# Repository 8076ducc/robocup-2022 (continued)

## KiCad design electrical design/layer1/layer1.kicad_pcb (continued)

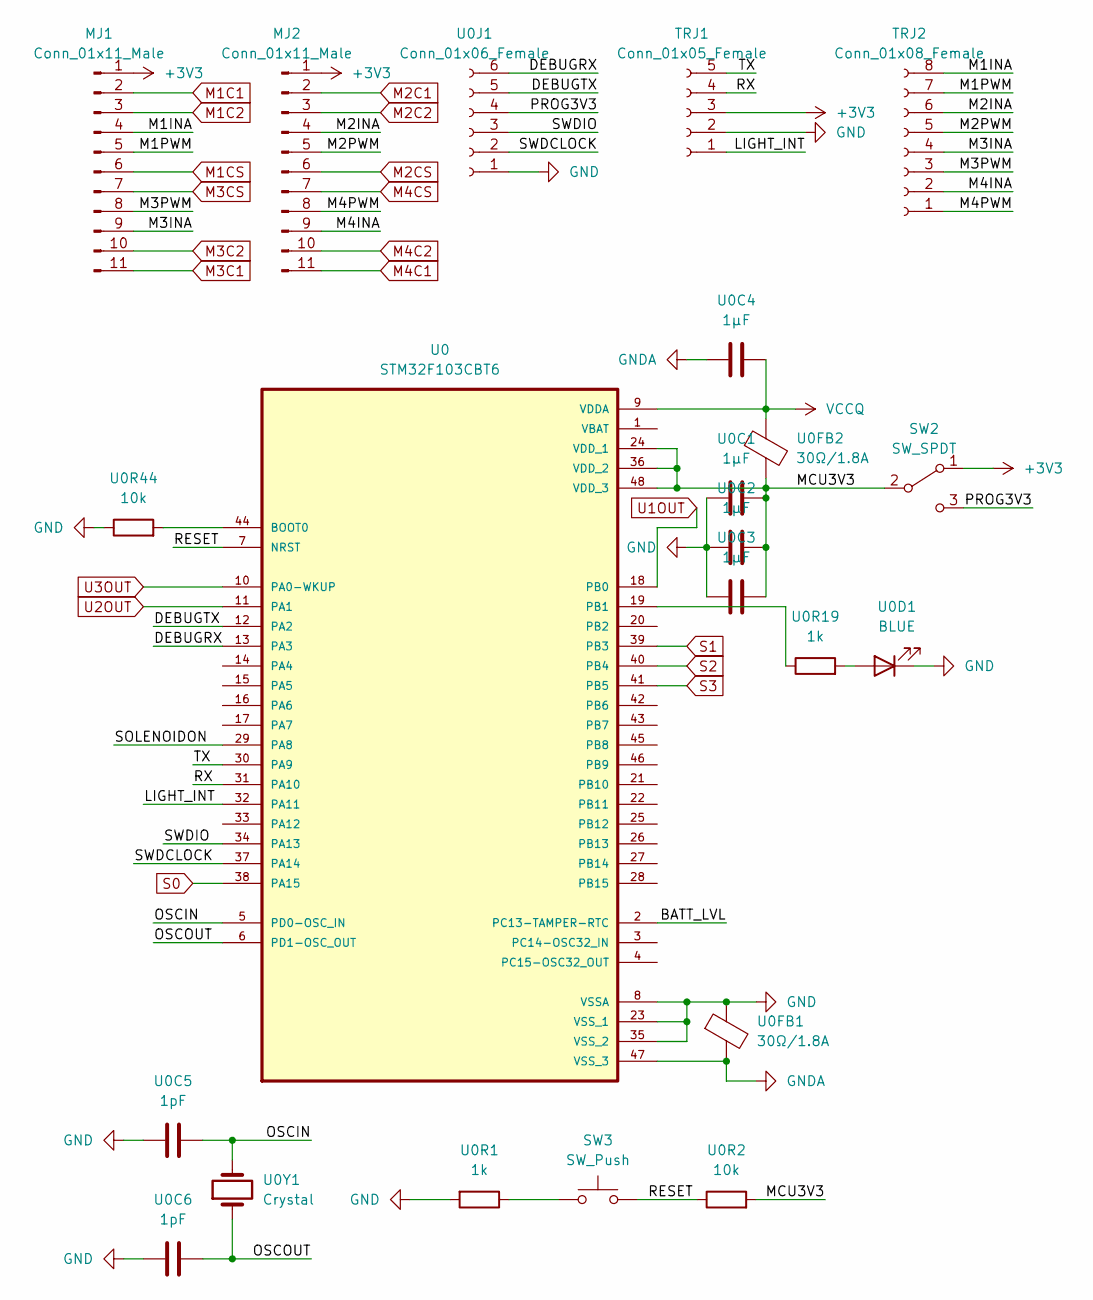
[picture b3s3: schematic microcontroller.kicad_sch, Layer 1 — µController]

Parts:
MJ1, MJ2: Conn_01x11_Male; 1X11_LOCK
SW2: SW_SPDT; SWITCH_SPDT_PTH_11.6X4.0MM_LOCK
SW3: SW_Push; SW_Push_SPST_NO_Alps_SKRK
TRJ1: Conn_01x05_Female; JST_SH_BM05B-SRSS-TB_1x05-1MP_P1.00mm_Vertical
TRJ2: Conn_01x08_Female; JST_SH_BM08B-SRSS-TB_1x08-1MP_P1.00mm_Vertical
U0: STM32F103CBT6; QFP50P900X900X160-48N; PARTREV 10
U0C1, U0C2, U0C3, U0C4: 1µF; 0603
U0C5, U0C6: 1pF; 0603
U0D1: BLUE; LED-0603
U0FB1, U0FB2: 30Ω/1.8A; 0603
U0J1: Conn_01x06_Female; JST_SH_BM06B-SRSS-TB_1x06-1MP_P1.00mm_Vertical
U0R1, U0R19: 1k; 0603
U0R2, U0R44: 10k; 0603
U0Y1: Crystal; CRYSTAL-SMD-5X3.2-2PAD

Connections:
+3V3: MJ1.1, MJ2.1, SW2.1 (A), TRJ1.3; also elsewhere on the board
/microcontroller/BATT_LVL: U0.2 (PC13-TAMPER-RTC)
/microcontroller/DEBUGRX: U0.13 (PA3), U0J1.6
/microcontroller/DEBUGTX: U0.12 (PA2), U0J1.5
/microcontroller/LIGHT_INT: TRJ1.1, U0.32 (PA11)
/microcontroller/M1INA: MJ1.4, TRJ2.8
/microcontroller/M1PWM: MJ1.5, TRJ2.7
/microcontroller/M2INA: MJ2.4, TRJ2.6
/microcontroller/M2PWM: MJ2.5, TRJ2.5
/microcontroller/M3INA: MJ1.9, TRJ2.4
/microcontroller/M3PWM: MJ1.8, TRJ2.3
/microcontroller/M4INA: MJ2.9, TRJ2.2
/microcontroller/M4PWM: MJ2.8, TRJ2.1
/microcontroller/MCU3V3: SW2.2 (B), U0.24 (VDD_1), U0.36 (VDD_2), U0.48 (VDD_3), U0C1.2, U0C2.2, U0C3.2, U0FB2.2, U0R2.2
/microcontroller/OSCIN: U0.5 (PD0-OSC_IN), U0C5.2, U0Y1.2
/microcontroller/OSCOUT: U0.6 (PD1-OSC_OUT), U0C6.2, U0Y1.1
/microcontroller/PROG3V3: SW2.3 (C), U0J1.4
/microcontroller/RESET: SW3.2, U0.7 (NRST), U0R2.1
/microcontroller/RX: TRJ1.4, U0.31 (PA10)
/microcontroller/SOLENOIDON: U0.29 (PA8)
/microcontroller/SWDCLOCK: U0.37 (PA14), U0J1.2
/microcontroller/SWDIO: U0.34 (PA13), U0J1.3
/microcontroller/TX: TRJ1.5, U0.30 (PA9)
GND: TRJ1.2, U0.8 (VSSA), U0.23 (VSS_1), U0.35 (VSS_2), U0C1.1, U0C2.1, U0C3.1, U0C5.1, U0C6.1, U0D1.1 (K), U0FB1.1, U0J1.1, U0R1.2, U0R44.1; also elsewhere on the board
GNDA: U0.47 (VSS_3), U0C4.1, U0FB1.2
M1C1: MJ1.2; also elsewhere on the board
M1C2: MJ1.3; also elsewhere on the board
M1CS: MJ1.6; also elsewhere on the board
M2C1: MJ2.2; also elsewhere on the board
M2C2: MJ2.3; also elsewhere on the board
M2CS: MJ2.6; also elsewhere on the board
M3C1: MJ1.11; also elsewhere on the board
M3C2: MJ1.10; also elsewhere on the board
M3CS: MJ1.7; also elsewhere on the board
M4C1: MJ2.11; also elsewhere on the board
M4C2: MJ2.10; also elsewhere on the board
M4CS: MJ2.7; also elsewhere on the board
unnamed: SW3.1, U0R1.1
unnamed: U0.19 (PB1), U0R19.1
unnamed: U0.44 (BOOT0), U0R44.2
unnamed: U0D1.2 (A), U0R19.2
S0: U0.38 (PA15); also elsewhere on the board
S1: U0.39 (PB3); also elsewhere on the board
S2: U0.40 (PB4); also elsewhere on the board
S3: U0.41 (PB5); also elsewhere on the board
U1OUT: U0.18 (PB0); also elsewhere on the board
U2OUT: U0.11 (PA1); also elsewhere on the board
U3OUT: U0.10 (PA0-WKUP); also elsewhere on the board
VCCQ: U0.9 (VDDA), U0C4.2, U0FB2.1; also elsewhere on the board

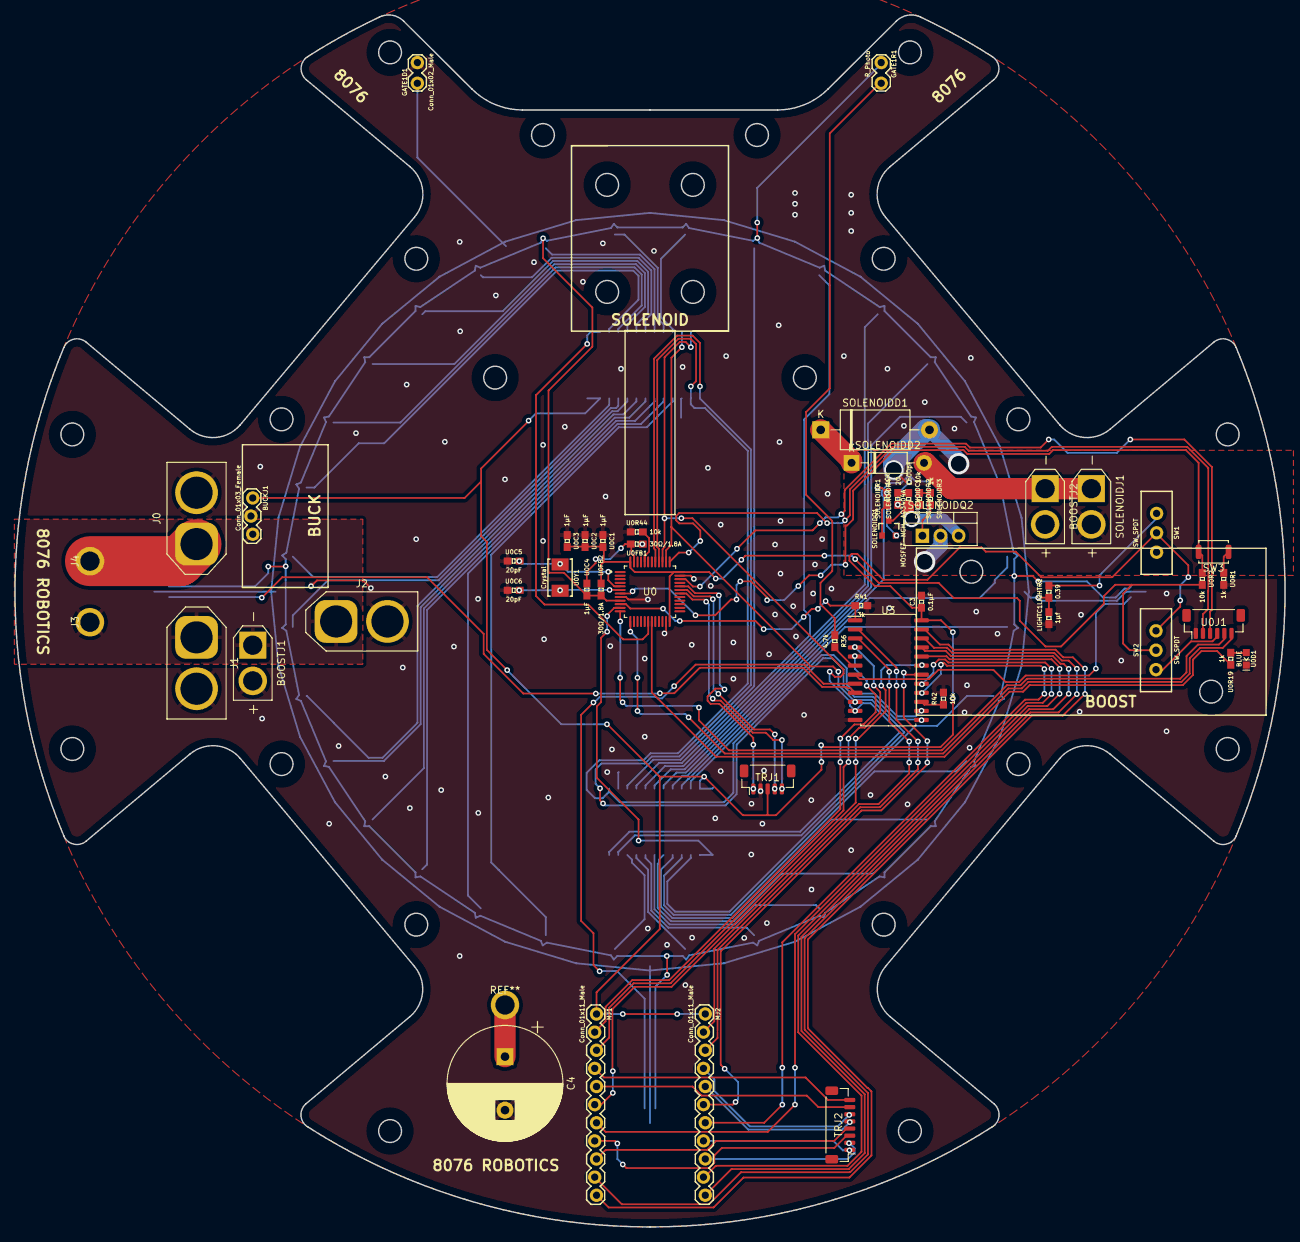
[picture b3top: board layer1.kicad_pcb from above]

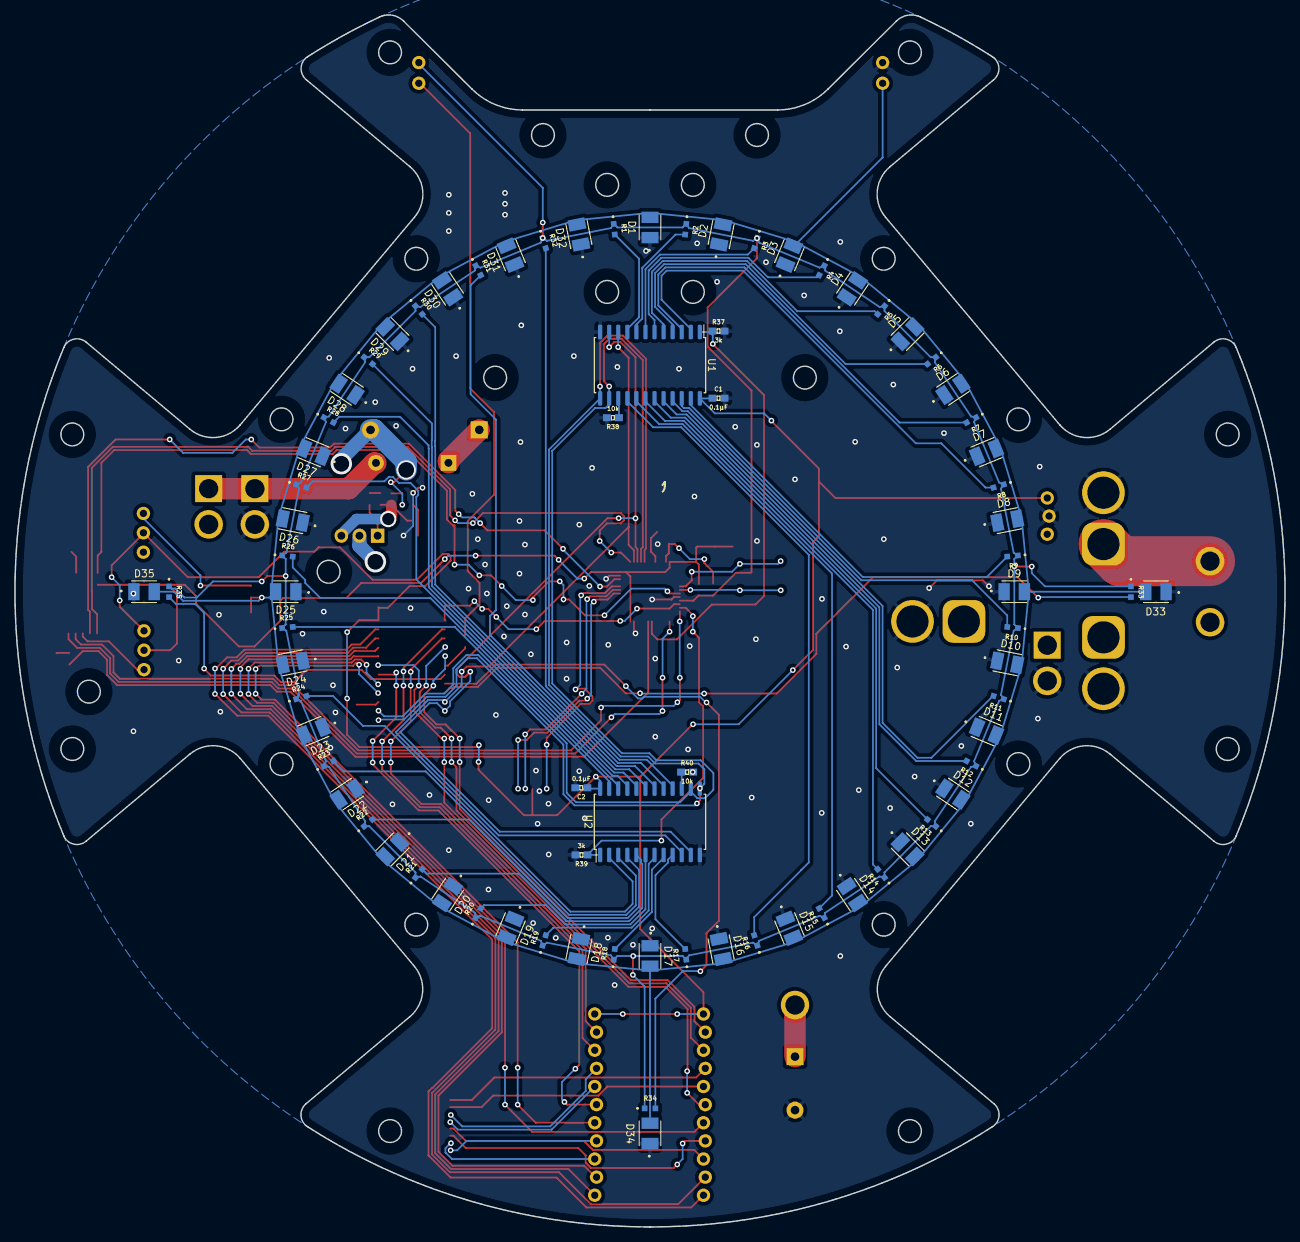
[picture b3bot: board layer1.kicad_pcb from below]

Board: 2 copper layers, 178.0 x 169.8 mm, 129 parts (78 on the bottom side), 99 nets.

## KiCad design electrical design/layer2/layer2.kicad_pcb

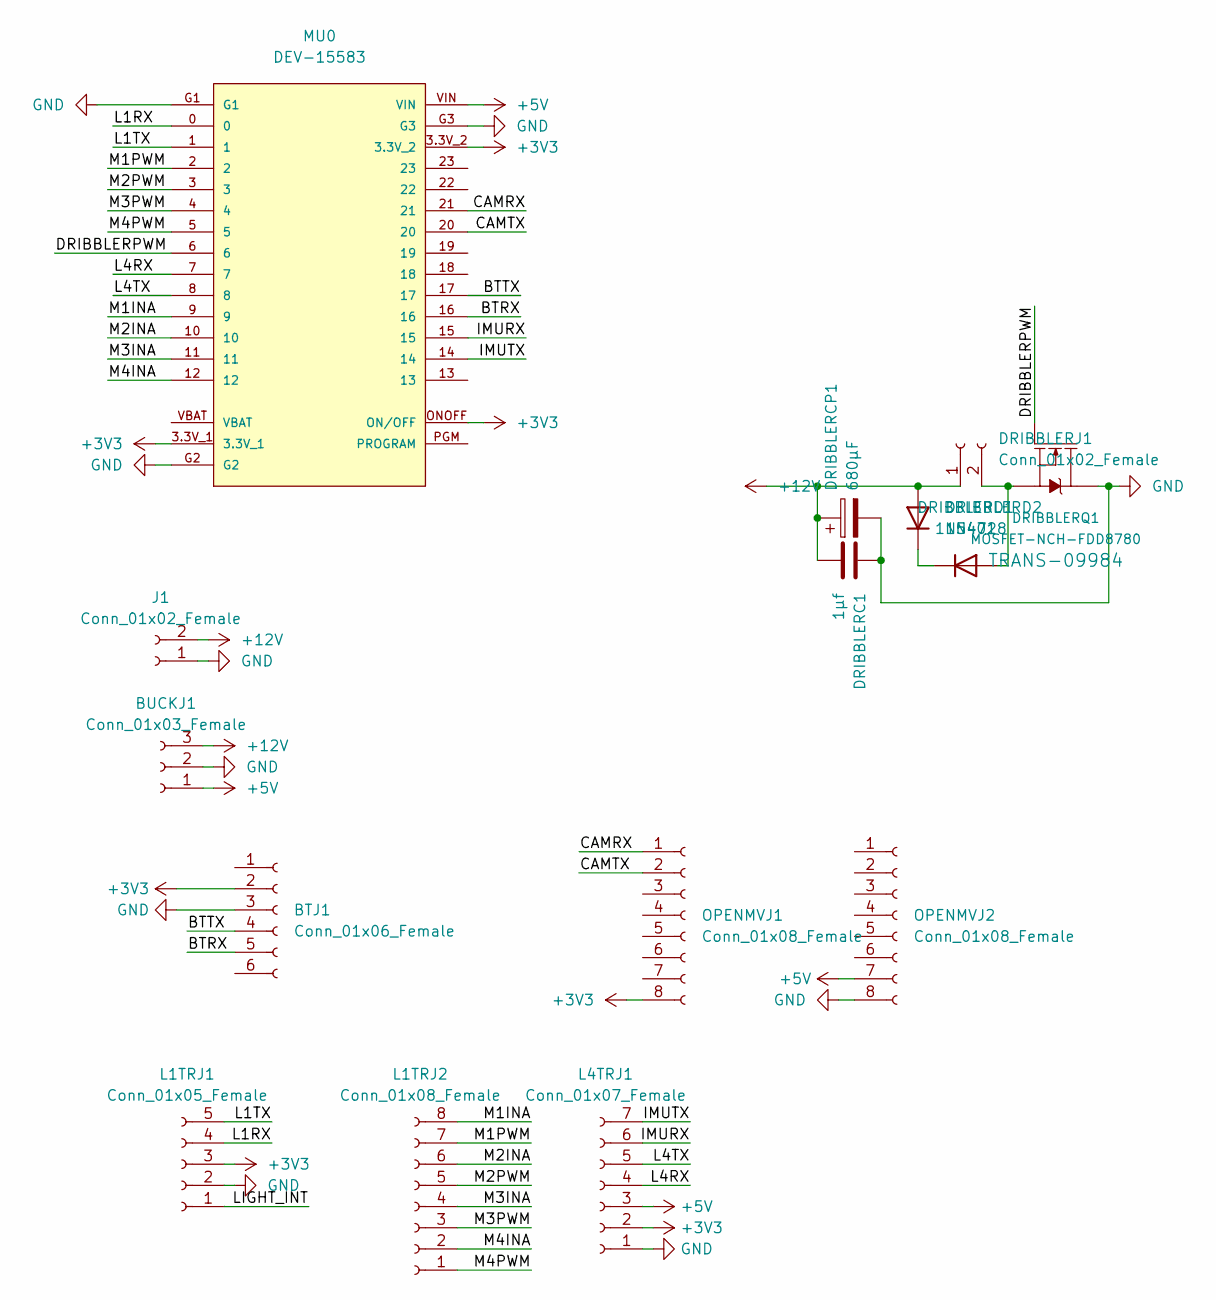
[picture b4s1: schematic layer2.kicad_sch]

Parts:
BTJ1: Conn_01x06_Female; 1X06_FEMALE_LOCK.010
BUCKJ1: Conn_01x03_Female; 1X03_LOCK
DRIBBLERC1: 1µf; 0603
DRIBBLERCP1: 680µF; CP_Radial_D8.0mm_P3.50mm
DRIBBLERD1: 1N5401; D_DO-27_P15.24mm_Horizontal
DRIBBLERD2: 1N4728; D_DO-41_SOD81_P10.16mm_Horizontal
DRIBBLERJ1: Conn_01x02_Female; AMASS_XT30PW-F_1x02_P2.50mm_Horizontal
DRIBBLERQ1: MOSFET-NCH-FDD8780; DPAK
J1: Conn_01x02_Female; AMASS_XT30PW-F_1x02_P2.50mm_Horizontal
L1TRJ1: Conn_01x05_Female; JST_SH_BM05B-SRSS-TB_1x05-1MP_P1.00mm_Vertical
L1TRJ2: Conn_01x08_Female; JST_SH_BM08B-SRSS-TB_1x08-1MP_P1.00mm_Vertical
L4TRJ1: Conn_01x07_Female; JST_SH_BM07B-SRSS-TB_1x07-1MP_P1.00mm_Vertical
MU0: DEV-15583; Teensy40
OPENMVJ1, OPENMVJ2: Conn_01x08_Female; 1X08_FEMALE_LOCK

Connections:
+3V3: BTJ1.2, L1TRJ1.3, L4TRJ1.2, MU0.3.3V_1, MU0.3.3V_2, MU0.ONOFF (ON/OFF), OPENMVJ1.8
+5V: BUCKJ1.1, L4TRJ1.3, MU0.VIN, OPENMVJ2.7
+12V: BUCKJ1.3, DRIBBLERC1.2, DRIBBLERCP1.1, DRIBBLERD2.2 (A), DRIBBLERJ1.1, J1.2
/BTRX: BTJ1.5, MU0.16
/BTTX: BTJ1.4, MU0.17
/CAMRX: MU0.21, OPENMVJ1.1
/CAMTX: MU0.20, OPENMVJ1.2
/DRIBBLERPWM: DRIBBLERQ1.1 (G), MU0.6
/IMURX: L4TRJ1.6, MU0.15
/IMUTX: L4TRJ1.7, MU0.14
/L1RX: L1TRJ1.4, MU0.0
/L1TX: L1TRJ1.5, MU0.1
/L4RX: L4TRJ1.4, MU0.7
/L4TX: L4TRJ1.5, MU0.8
/LIGHT_INT: L1TRJ1.1
/M1INA: L1TRJ2.8, MU0.9
/M1PWM: L1TRJ2.7, MU0.2
/M2INA: L1TRJ2.6, MU0.10
/M2PWM: L1TRJ2.5, MU0.3
/M3INA: L1TRJ2.4, MU0.11
/M3PWM: L1TRJ2.3, MU0.4
/M4INA: L1TRJ2.2, MU0.12
/M4PWM: L1TRJ2.1, MU0.5
GND: BTJ1.3, BUCKJ1.2, DRIBBLERC1.1, DRIBBLERCP1.2, DRIBBLERQ1.4 (D), J1.1, L1TRJ1.2, L4TRJ1.1, MU0.G1, MU0.G2, MU0.G3, OPENMVJ2.8
unnamed: DRIBBLERD1.1 (K), DRIBBLERD2.1 (K)
unnamed: DRIBBLERD1.2 (A), DRIBBLERJ1.2, DRIBBLERQ1.3 (S)

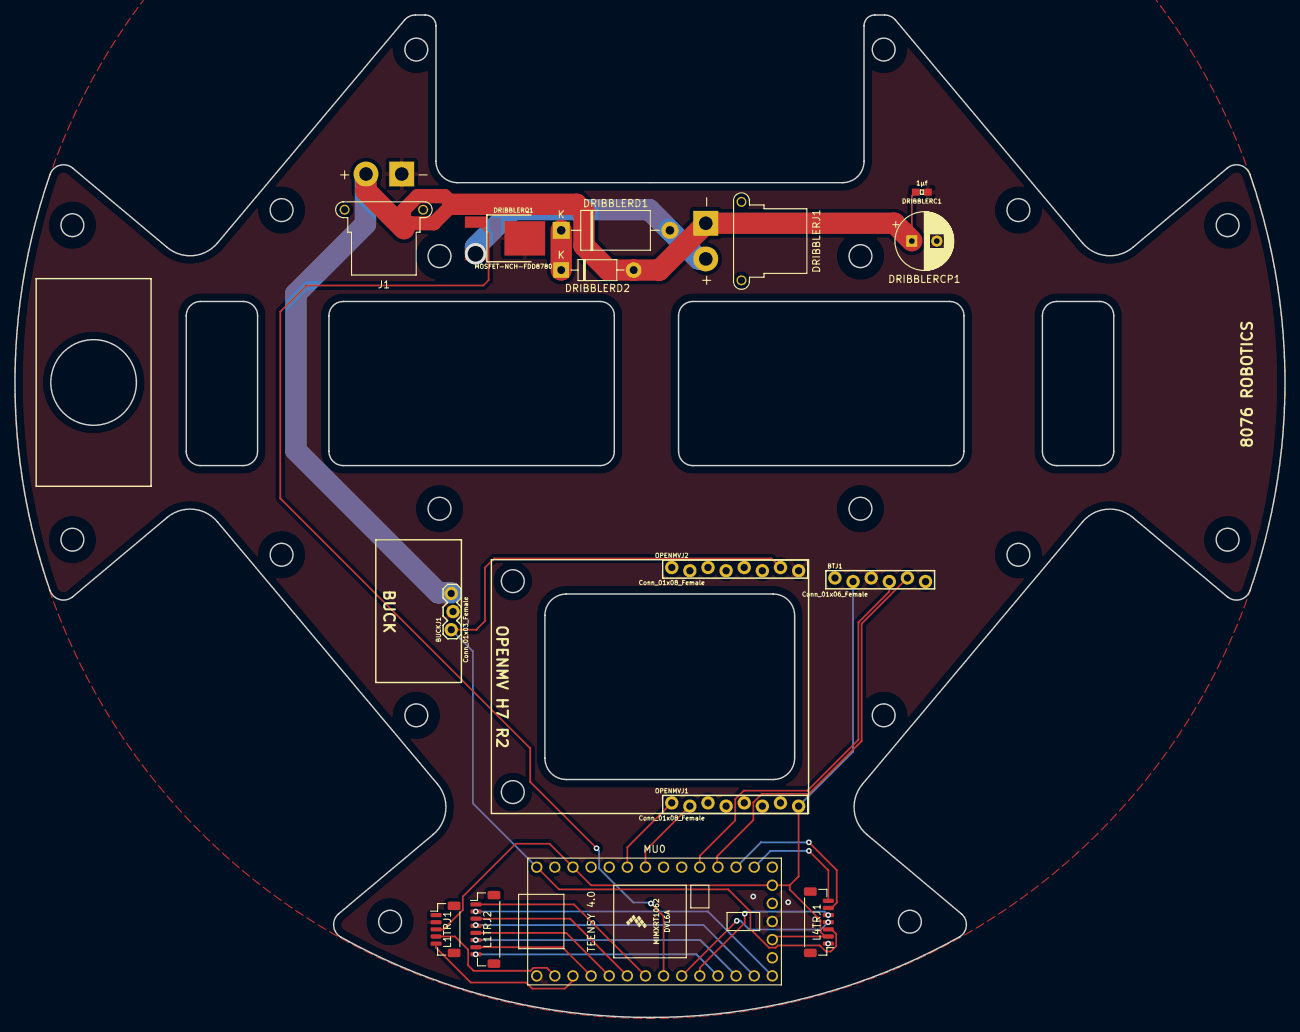
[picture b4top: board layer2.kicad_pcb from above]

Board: 2 copper layers, 178.0 x 140.5 mm, 15 parts (0 on the bottom side), 25 nets.

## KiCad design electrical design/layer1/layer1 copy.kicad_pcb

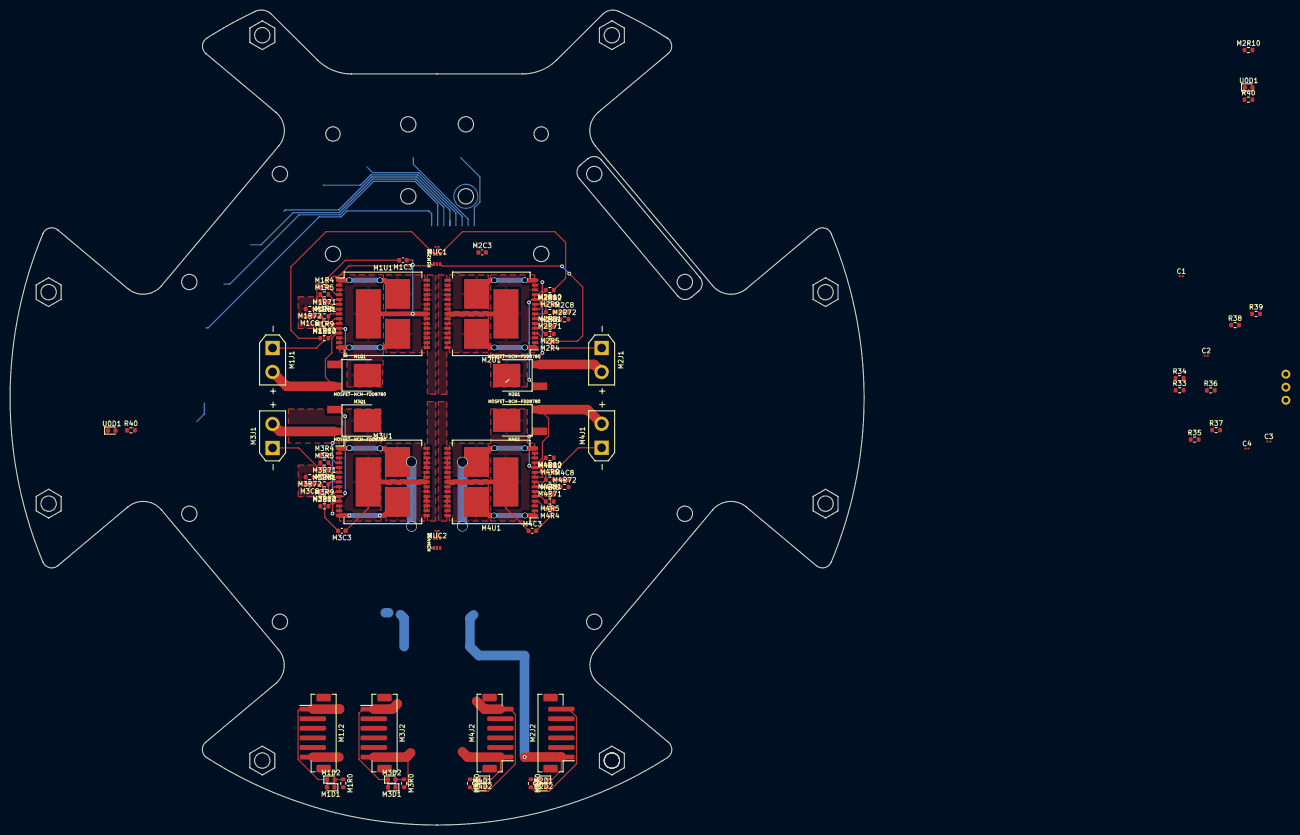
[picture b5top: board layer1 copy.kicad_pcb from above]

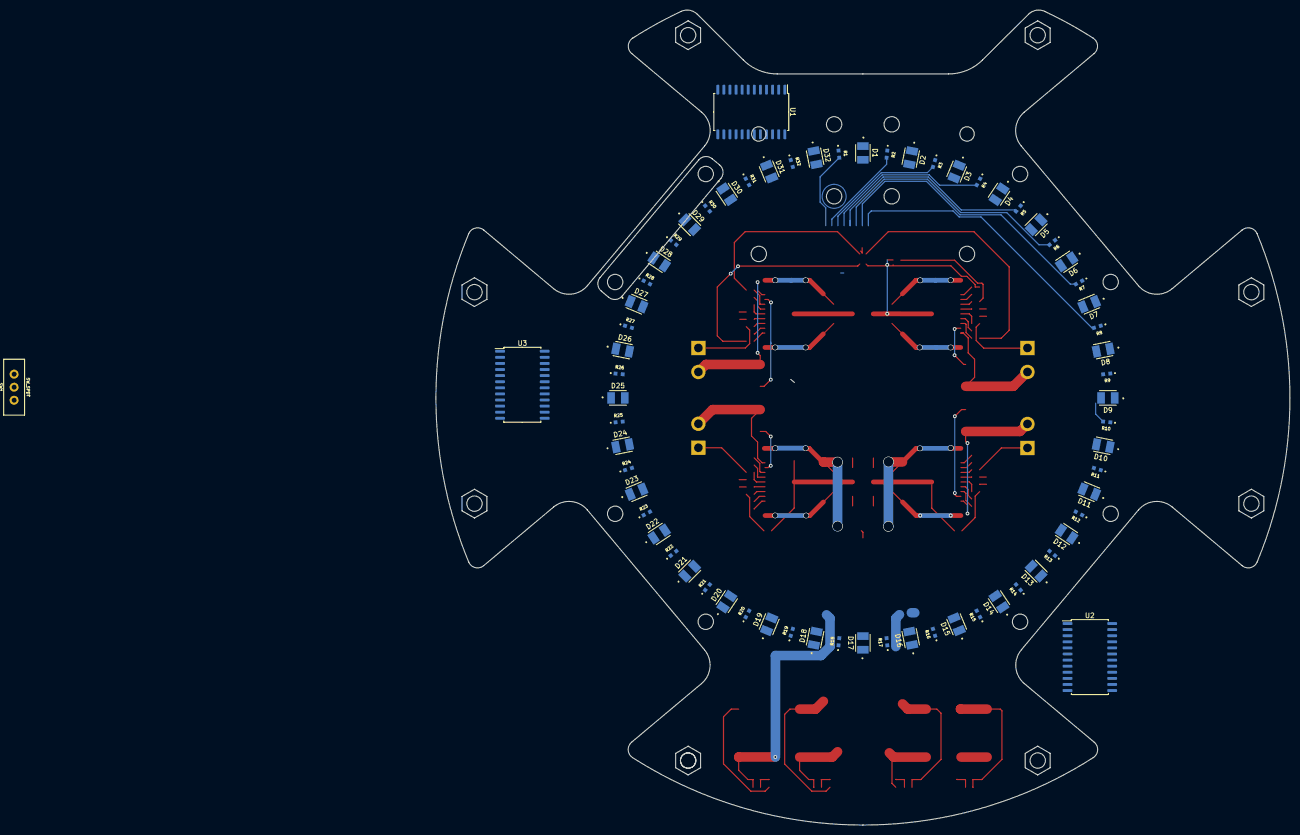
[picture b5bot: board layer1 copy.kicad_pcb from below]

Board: 2 copper layers, 178.0 x 169.8 mm, 160 parts (68 on the bottom side), 121 nets.

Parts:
C1, C3, C4: 0.1µF; C_0201_0603Metric
C2: 1µf; C_0201_0603Metric
D1, D2, D3, D4, D5, D6, D7, D8, D9, D10, D11, D12, D13, D14, D15, D16, D17, D18, D19, D20, D21, D22, D23, D24, D25, D26, D27, D28, D29, D30, D31, D32: LED; LED_OF-SMD3528WC
M1C3, M2C3, M3C3, M4C3: 1µf; C_0603_1608Metric
M1C8, M2C8, M3C8, M4C8: 33nF; C_0603_1608Metric
M1D1, M2D1, M3D1, M4D1: RED; LED_0603_1608Metric
M1D2, M2D2, M3D2, M4D2: GREEN; LED_0603_1608Metric
M1J1, M2J1, M3J1, M4J1: Conn_01x02_Female; AMASS_XT30UPB-F_1x02_P5.0mm_Vertical
M1J2, M2J2, M3J2, M4J2: Conn_01x06_Female; JST_PH_B6B-PH-SM4-TB_1x06-1MP_P2.00mm_Vertical
M1M2U1, M3M4U1: 74LVC2G07GW,125; SOP65P210X110-6N
M1Q1, M2Q1, M3Q1, M4Q1: MOSFET-NCH-FDD8780; DPAK
M1R0, M2R0, M3R0, M4R0: 4.7k; R_0603_1608Metric
M1R4, M1R10, M1R71, M1R82, M2R4, M2R10, M2R10#2, M2R71, M2R82, M3R4, M3R10, M3R71, M3R82, M4R4, M4R10, M4R71, M4R82: 1k; R_0603_1608Metric
M1R5, M1R9, M2R5, M2R9, M3R5, M3R9, M4R5, M4R9: 3.24k; R_0603_1608Metric
M1R6, M1R72, M1R81, M2R6, M2R72, M2R81, M3R6, M3R72, M3R81, M4R6, M4R72, M4R81: 10k; R_0603_1608Metric
M1U1, M2U1, M3U1, M4U1: VNH5019A-E; ST_MultiPowerSO-30
MUC1, MUC2: 0.1µF; C_0201_0603Metric
R1, R2, R3, R4, R5, R6, R7, R8, R9, R10, R11, R12, R13, R14, R15, R16, R17, R18, R19, R20, R21, R22, R23, R24, R25, R26, R27, R28, R29, R30, R31, R32: R_Photo; XDCR_ALS-PT19-315C_L177_TR8
R33, R35, R38: 3k; R_0603_1608Metric
R34, R37, R39: 10k; R_0603_1608Metric
R36: 0.39; R_0603_1608Metric
R40, R40#2: R; R_0603_1608Metric
SW1: SW_SPDT; SWITCH_SPDT_PTH_11.6X4.0MM_LOCK
U0D1, U0D1#2: BLUE; LED_0603_1608Metric
U1, U2, U3: CD74HC4067M; SOIC-24W_7.5x15.4mm_P1.27mm

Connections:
+3V3: C1.1, C1.2, C2.2, C3.1, C3.2, C4.2, D1.1 (K), D2.1 (K), D3.1 (K), D4.1 (K), D5.1 (K), D6.1 (K), D7.1 (K), D8.1 (K), D9.1 (K), D10.1 (K), D11.1 (K), D12.1 (K), D13.1 (K), D14.1 (K), D15.1 (K), D16.1 (K), D17.1 (K), D18.1 (K), D19.1 (K), D20.1 (K), D21.1 (K), D22.1 (K), D23.1 (K), D24.1 (K), D25.1 (K), D26.1 (K), D27.1 (K), D28.1 (K), D29.1 (K), D30.1 (K), D31.1 (K), D32.1 (K), M1J2.5, M1M2U1.2 (GND), M1M2U1.5 (VCC), M1R5.1, M1R9.1, M2J2.5, M2R5.1, M2R9.1, M3J2.5, M3M4U1.2 (GND), M3M4U1.5 (VCC), M3R5.1, M3R9.1, M4J2.5, M4R5.1, M4R9.1, MUC1.1, MUC1.2, MUC2.1, MUC2.2, R1.1, R2.1, R3.1, R4.1, R5.1, R6.1, R7.1, R8.1, R9.1, R10.1, R11.1, R12.1, R13.1, R14.1, R15.1, R16.1, R17.1, R18.1, R19.1, R20.1, R21.1, R22.1, R23.1, R24.1, R25.1, R26.1, R27.1, R28.1, R29.1, R30.1, R31.1, R32.1, R33.2, R34.2, R35.2, R37.2, R38.2, R39.2, U0D1.1 (K), U0D1#2.1 (K), U1.12 (GND), U1.24 (VCC), U2.12 (GND), U2.24 (VCC), U3.12 (GND)
/drive/M1CP: M1Q1.1 (G), M1U1.11 (CP)
/drive/M1CS: M1C8.1, M1R81.1
/drive/M1CSDIS: M1R6.1, M1U1.6 (CS_DIS)
/drive/M1INA: M1M2U1.1 (1A), M1R4.1
/drive/M1INB: M1M2U1.6 (1Y), M1R10.1
/drive/M1OUTA: M1J2.6, M1R0.2, M1U1.1 (OUTA), M1U1.25 (OUTA), M1U1.30 (OUTA), M1U1.33 (OUTA)
/drive/M1OUTB: M1D1.2 (A), M1D2.1 (K), M1J2.1, M1U1.15 (OUTB), M1U1.16 (OUTB), M1U1.21 (OUTB), M1U1.32 (OUTB)
/drive/M1PWM: M1R71.1, M1R72.1
/drive/M2CP: M2Q1.1 (G), M2U1.11 (CP)
/drive/M2CS: M2C8.1, M2R81.1
/drive/M2CSDIS: M2R6.1, M2U1.6 (CS_DIS)
/drive/M2INA: M1M2U1.3 (2A), M2R4.1
/drive/M2INB: M1M2U1.4 (2Y), M2R10.1, M2R10#2.1
/drive/M2OUTA: M2J2.6, M2R0.2, M2U1.1 (OUTA), M2U1.25 (OUTA), M2U1.30 (OUTA), M2U1.33 (OUTA)
/drive/M2OUTB: M2D1.2 (A), M2D2.1 (K), M2J2.1, M2U1.15 (OUTB), M2U1.16 (OUTB), M2U1.21 (OUTB), M2U1.32 (OUTB)
/drive/M2PWM: M2R71.1, M2R72.1
/drive/M3CP: M3Q1.1 (G), M3U1.11 (CP)
/drive/M3CS: M3C8.1, M3R81.1
/drive/M3CSDIS: M3R6.1, M3U1.6 (CS_DIS)
/drive/M3INA: M3M4U1.1 (1A), M3R4.1
/drive/M3INB: M3M4U1.6 (1Y), M3R10.1
/drive/M3OUTA: M3J2.6, M3R0.2, M3U1.1 (OUTA), M3U1.25 (OUTA), M3U1.30 (OUTA), M3U1.33 (OUTA)
/drive/M3OUTB: M3D1.2 (A), M3D2.1 (K), M3J2.1, M3U1.15 (OUTB), M3U1.16 (OUTB), M3U1.21 (OUTB), M3U1.32 (OUTB)
/drive/M3PWM: M3R71.1, M3R72.1
/drive/M4CP: M4Q1.1 (G), M4U1.11 (CP)
/drive/M4CS: M4C8.1, M4R81.1
/drive/M4CSDIS: M4R6.1, M4U1.6 (CS_DIS)
/drive/M4INA: M3M4U1.3 (2A), M4R4.1
/drive/M4INB: M3M4U1.4 (2Y), M4R10.1
/drive/M4OUTA: M4J2.6, M4R0.2, M4U1.1 (OUTA), M4U1.25 (OUTA), M4U1.30 (OUTA), M4U1.33 (OUTA)
/drive/M4OUTB: M4D1.2 (A), M4D2.1 (K), M4J2.1, M4U1.15 (OUTB), M4U1.16 (OUTB), M4U1.21 (OUTB), M4U1.32 (OUTB)
/drive/M4PWM: M4R71.1, M4R72.1
/led/LSOUT1: R33.1, U1.1 (COM)
/led/LSOUT2: R35.1, U2.1 (COM)
/led/LSOUT3: R38.1, U3.1 (COM)
/led/S0: U1.10 (S0), U2.10 (S0), U3.10 (S0)
/led/S1: U1.11 (S1), U2.11 (S1), U3.11 (S1)
/led/S2: U1.14 (S2), U2.14 (S2), U3.14 (S2)
/led/S3: U1.13 (S3), U2.13 (S3), U3.13 (S3)
unnamed: C4.1, U3.24 (VCC)
unnamed: C2.1, D1.2 (A), D2.2 (A), D3.2 (A), D4.2 (A), D5.2 (A), D6.2 (A), D7.2 (A), D8.2 (A), D9.2 (A), D10.2 (A), D11.2 (A), D12.2 (A), D13.2 (A), D14.2 (A), D15.2 (A), D16.2 (A), D17.2 (A), D18.2 (A), D19.2 (A), D20.2 (A), D21.2 (A), D22.2 (A), D23.2 (A), D24.2 (A), D25.2 (A), D26.2 (A), D27.2 (A), D28.2 (A), D29.2 (A), D30.2 (A), D31.2 (A), D32.2 (A), R36.2
unnamed: M1C3.1, M1Q1.4 (D), M1U1.3 (VCC), M1U1.13 (VCC), M1U1.23 (VCC), M1U1.31 (VCC)
unnamed: M1C3.2, M1C8.2, M1J1.1, M1R6.2, M1R72.2, M1R82.2, M1U1.18 (GNDB), M1U1.19 (GNDB), M1U1.20 (GNDB), M1U1.26 (GNDA), M1U1.27 (GNDA), M1U1.28 (GNDA)
unnamed: M1D1.1 (K), M1D2.2 (A), M1R0.1
unnamed: M1J1.2, M1Q1.3 (S), M1U1.12 (VBAT)
unnamed: M1R4.2, M1U1.4 (INA)
unnamed: M1R5.2, M1U1.5 (EN/DIAGA)
unnamed: M1R9.2, M1U1.9 (EN/DIAGB)
unnamed: M1R10.2, M1U1.10 (INB)
unnamed: M1R71.2, M1U1.7 (PWM)
unnamed: M1R81.2, M1R82.1, M1U1.8 (CS)
unnamed: M2C3.1, M2Q1.4 (D), M2U1.3 (VCC), M2U1.13 (VCC), M2U1.23 (VCC), M2U1.31 (VCC)
unnamed: M2C3.2, M2C8.2, M2J1.1, M2R6.2, M2R72.2, M2R82.2, M2U1.18 (GNDB), M2U1.19 (GNDB), M2U1.20 (GNDB), M2U1.26 (GNDA), M2U1.27 (GNDA), M2U1.28 (GNDA)
unnamed: M2D1.1 (K), M2D2.2 (A), M2R0.1
unnamed: M2J1.2, M2Q1.3 (S), M2U1.12 (VBAT)
unnamed: M2R4.2, M2U1.4 (INA)
unnamed: M2R5.2, M2U1.5 (EN/DIAGA)
unnamed: M2R9.2, M2U1.9 (EN/DIAGB)
unnamed: M2R10.2, M2R10#2.2, M2U1.10 (INB)
unnamed: M2R71.2, M2U1.7 (PWM)
unnamed: M2R81.2, M2R82.1, M2U1.8 (CS)
unnamed: M3C3.1, M3Q1.4 (D), M3U1.3 (VCC), M3U1.13 (VCC), M3U1.23 (VCC), M3U1.31 (VCC)
unnamed: M3C3.2, M3C8.2, M3J1.1, M3R6.2, M3R72.2, M3R82.2, M3U1.18 (GNDB), M3U1.19 (GNDB), M3U1.20 (GNDB), M3U1.26 (GNDA), M3U1.27 (GNDA), M3U1.28 (GNDA)
unnamed: M3D1.1 (K), M3D2.2 (A), M3R0.1
unnamed: M3J1.2, M3Q1.3 (S), M3U1.12 (VBAT)
unnamed: M3R4.2, M3U1.4 (INA)
unnamed: M3R5.2, M3U1.5 (EN/DIAGA)
unnamed: M3R9.2, M3U1.9 (EN/DIAGB)
unnamed: M3R10.2, M3U1.10 (INB)
unnamed: M3R71.2, M3U1.7 (PWM)
unnamed: M3R81.2, M3R82.1, M3U1.8 (CS)
unnamed: M4C3.1, M4Q1.4 (D), M4U1.3 (VCC), M4U1.13 (VCC), M4U1.23 (VCC), M4U1.31 (VCC)
unnamed: M4C3.2, M4C8.2, M4J1.1, M4R6.2, M4R72.2, M4R82.2, M4U1.18 (GNDB), M4U1.19 (GNDB), M4U1.20 (GNDB), M4U1.26 (GNDA), M4U1.27 (GNDA), M4U1.28 (GNDA)
unnamed: M4D1.1 (K), M4D2.2 (A), M4R0.1
unnamed: M4J1.2, M4Q1.3 (S), M4U1.12 (VBAT)
unnamed: M4R4.2, M4U1.4 (INA)
unnamed: M4R5.2, M4U1.5 (EN/DIAGA)
unnamed: M4R9.2, M4U1.9 (EN/DIAGB)
unnamed: M4R10.2, M4U1.10 (INB)
unnamed: M4R71.2, M4U1.7 (PWM)
unnamed: M4R81.2, M4R82.1, M4U1.8 (CS)
unnamed: R1.2, U1.9 (I0)
unnamed: R2.2, U1.8 (I1)
unnamed: R3.2, U1.7 (I2)
unnamed: R4.2, U1.6 (I3)
unnamed: R5.2, U1.5 (I4)
unnamed: R6.2, U1.4 (I5)
unnamed: R7.2, U1.3 (I6)
unnamed: R8.2, U1.2 (I7)
unnamed: R9.2, U1.23 (I8)
unnamed: R10.2, U1.22 (I9)
unnamed: R11.2, U1.21 (I10)
unnamed: R12.2, U1.20 (I11)
unnamed: R13.2, U1.19 (I12)
unnamed: R14.2, U1.18 (I13)
unnamed: R15.2, U1.17 (I14)
unnamed: R16.2, U1.16 (I15)
unnamed: R17.2, U2.9 (I0)
unnamed: R18.2, U2.8 (I1)
unnamed: R19.2, U2.7 (I2)
unnamed: R20.2, U2.6 (I3)
unnamed: R21.2, U2.5 (I4)
unnamed: R22.2, U2.4 (I5)
unnamed: R23.2, U2.3 (I6)
unnamed: R24.2, U2.2 (I7)
unnamed: R25.2, U2.23 (I8)
unnamed: R26.2, U2.22 (I9)
unnamed: R27.2, U2.21 (I10)
unnamed: R28.2, U2.20 (I11)
unnamed: R29.2, U2.19 (I12)
unnamed: R30.2, U2.18 (I13)
unnamed: R31.2, U2.17 (I14)
unnamed: R32.2, U2.16 (I15)
unnamed: R34.1, U1.15 (~E)
unnamed: R36.1, SW1.3 (C)
unnamed: R37.1, U2.15 (~E)
unnamed: R39.1, U3.15 (~E)
unnamed: R40.1, R40#2.1
unnamed: R40.2, R40#2.2, U0D1.2 (A), U0D1#2.2 (A)
VCC: M1J2.2, M2J2.2, M3J2.2, M4J2.2

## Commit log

2022-04-09 finish electrical design
2022-04-09 fix some gitignore issues
2022-04-14 add board cutouts
2022-04-14 add omniwheel 3dp files
2022-06-18 rename some files
